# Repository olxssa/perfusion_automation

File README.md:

# perfusion_automation

*Design and implementation of an automated high-content screening cell perfusion system, including associated control software*

Here, the design, implementation and benchmarking of a fully integrated, modular screening platform for automated, multiplexed bath perfusion experiments is documented. 
The system was developed to provide reproducible and sample-friendly solution exchange for optical characterization of biosensors.

The platform consists of three primary systems: a modular fluorescence microscope, an automated bath perfusion add-on, and an integrated hardware and software control framework. 

## Repository Content

### FreeCAD Files
Using the software FreeCAD, the provided CAD files can be exported as .stl and 3D-printed using PLA, 15 % infill and 0.2 mm layer height. 
Alternatively, the files can be adapted to your liking.

### FPC Design Files
In order to create a more elegant design for controlling the microvalves, a custom Flexible Printed Circuit (FPC) was designed using KiCAD in accordance with the information given by the company memetis. 
The microvalves are controlled via a constant-current source. 
The valves are all connected in series and can each be bypassed on the circuit board using a MOSFET, with a tap between the valve contacts. 
This allows individual valves to be removed from the current path and taken out of the control circuit.

Custom-designed flexible printed circuit (FPC) for ECU-I 8CH and eight microvalves positioned on two 4-valve adapters and one 2-valve adapter. 
(**A**) Top-view of perfusion arm where 8 individual cables were connected to the controller adapter. 
(**B**) The PCB layer of the custom-designed FPC in KiCAD. 
(**C**) Top-view of the perfusion arm with the FPC.

### Firmware and MMConfig
Low-level hardware management is split between two microcontrollers and using the firmware rx_system.ino and tx_system.ino. 
High-level microscope hardware control is achieved via Pycro-Manager [1], 
which bridges the Python backend to a headless Java-based Micro-Manager [2] (v2.0.3) instance over port 4721.
The Micro-Manager instance is created using the config file MMConfig.cfg.

### Software

After the build, the setup can be controlled via a custom-developed web application called "Automated Bath Perfusion App". 
The web application serves as a single-page dashboard designed to organize all operational controls into three dedicated panels arranged from left to right:
* Preview:
   * Preview window featuring modes live, BF snap and fluorescence snap
   * Choose ideal fluorescence exposure time for your experiment
   * Choose indeal BF light source brightness for the software autofocus to work with your samples
   * Manual stage movement
   * Choose ideal software autofocus parameters for your experiment
   * Test flow from reservoirs 1-5
* Perfusion Experiment:
   * Set folder location to save all experiment files
   * Multi-well plate-type tool
   * Set imaging parameters: observation time after perfusion and imaging frequency
   * Name reservoirs accordingly to perfusate solutions
   * Set solution sequence and volumes to be perfused
   * Additional tools:
      * CenterFOV: By default, the well center coordinates are used as Field of View
      * AutoFOV: Automatically determine best Field of View for every well
      * ManuFOV: Manually determine best Field of View and focus position for every well
* Preliminary Analysis:
   * Cell segmentation of first fluorescence image for every well
   * Dynamic classification of cells that are fluorescent
   * Background subtraction and computation of fluorescence change over time for individual cells for every well
   * Comparison of mean of fluorescence change over time for all wells

### Data
The system's performance is validated by assessing pipetting procedures, 
demonstrating software autofocus stability and conducting automated multiplexed perfusion on cells expressing GFP and NEMO-based calcium sensors under agonist conditions.

## Documentation of the Project
### 1. Building a Modular Fluorescence Microscope

Schematic optical light path of the modular fluorescence microscope.

### 2. Constructing an Automated Bath Perfusion System for Screening

Implementation of the automated bath perfusion system. 
(**A**) The complete automated screening perfusion system integrated into the modular fluorescence microscope. 
(**B**)  The perfusion arm responsible for movement of tubes into single wells and for the perfusion and aspiration of the desired solution.

#### Fluidic Circuit

Wiring of the fluidic circuit. 
(**A**) Pressure distribution system. 
(**B**) Reservoirs with perfusion solutions. 
(**C**) Microvalve circuit and channel numbering. 
(**D**) Perfusion site with precise volume exchange.

#### Electrical Circuits

Wiring of the electrical circuits. 
(**A**) The RX system receives signals from the PC and controls the servo motors, the stepper motor drivers, relays (switchable power socket, 3/2-valve relays), and the Neopixel LED ring. 
(**B**) The TX system gathers information from the flow-rate sensor, the fluid level sensors and the stop button and sends the information to the PC.

### 3. Developing a Custom Web App as a User Interface using Flask

Web App Architecture. Multi-layered system showing the interaction between green software layers, blue hardware nodes, and the physical microscope components in grey.

Perfusion experiment workflow sequence. (**A**) Initialization and sensor validation. (**B**) Automated well
traversal, solution perfusion, and imaging loops. (**C**) Decontamination protocol and park execution.

### 4. Calibration and Benchmarking

Flow-rate stability characterization. 
(**A**)  Flow-rate robustness and transient oscillations observed during operational tuning. 
(**B**)  Flow-rate decay resulting from increased system resistance upon integrating additional reservoirs. 
(**C**)  Hydrostatic flow-rate decay as reservoir fluid levels deplete (tested across 100 mL, 50 mL, and 10 mL capacities). 
Modularity allows for interchangeable reservoir sizes to accommodate varying experimental volume requirements.

Software autofocus performance throughout a 6-well plate. 
For each well, except for the starting position A1, a course scan followed by a fine scan are carried out as shown on the left, resulting in a focussed sample shown on the right of each well.

<div style="display: flex; align-items: center; gap: 20px;">

</div>

Bath perfusion experiment with GFP (left) and NEMO (right) tagged ND cells. (**A**) Fluorescence overlay with segmented masks detected by Cellpose. The green outlines are the cells labeled as fluorescent, the black outlines show the rest of the segmented cells. (**B**) Physiological fluorescence intensity change / SBR of single cells (grey) and mean (red). (**C**) Mean trajectories of all wells for comparison.

### References

[1] H. Pinkard, N. Stuurman, I. E. Ivanov, et al., “Pycro-manager: Open-source software for customized and
reproducible microscope control,” Nat Methods, vol. 18, 226–228, 2021. DOI: 10.1038/s41592-021-01087-6.

[2] A. D. Edelstein, M. A. Tsuchida, N. Amodaj, H. Pinkard, R. D. Vale, and N. Stuurman, “Advanced methods of
microscope control using μmanager software,” Journal of Biological Methods, 2014. DOI: 10.14440/jbm.2014.36.

[3] J. Li, Z. Shang, J. H. Chen, et al., “Engineering of nemo as calcium indicators with large dynamics and high
sensitivity,” Nature Methods, vol. 20, pp. 918–924, 2023. DOI: 10.1038/s41592-023-01852-9.

[4] P. Dettinger, T. Kull, G. Arekatla, et al., “Open-source personal pipetting robots with live-cell incubation and
microscopy compatibility,” Nature Communications, vol. 13, no. 1, p. 2999, 2022. DOI: 10.1038/s41467-
022-30643-7.

### Demonstration Video: 
 Version: October 2026

Click on image to play on Youtube.com

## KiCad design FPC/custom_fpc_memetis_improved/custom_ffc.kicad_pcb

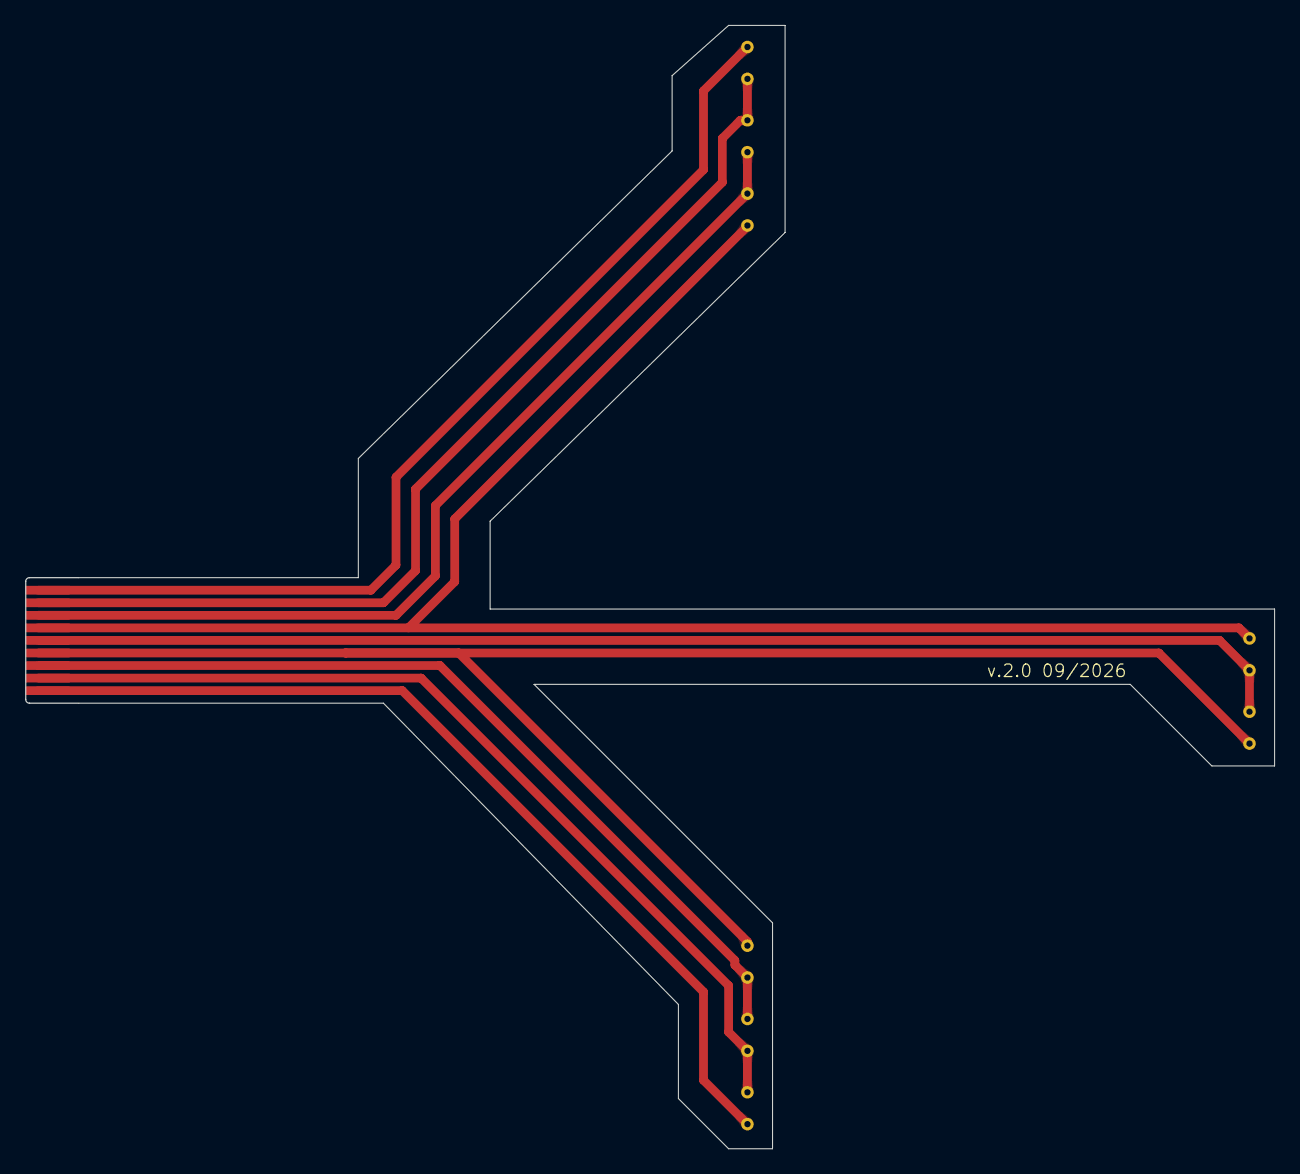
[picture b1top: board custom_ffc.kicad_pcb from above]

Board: 2 copper layers, 99.5 x 89.5 mm, 8 parts (0 on the bottom side), 7 nets.

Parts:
J1, J2, J3, J4, J5, J6, J7, J8: Conn_01x02_Pin; memetis_01x02

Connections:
unnamed: J1.2, J2.1
unnamed: J2.2, J3.1
unnamed: J3.2, J4.1
unnamed: J4.2, J5.1
unnamed: J5.2, J6.1
unnamed: J6.2, J7.1
unnamed: J7.2, J8.1

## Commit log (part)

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2025-12-11 Functions for multi-well perfusion
2026-01-02 Images for README
